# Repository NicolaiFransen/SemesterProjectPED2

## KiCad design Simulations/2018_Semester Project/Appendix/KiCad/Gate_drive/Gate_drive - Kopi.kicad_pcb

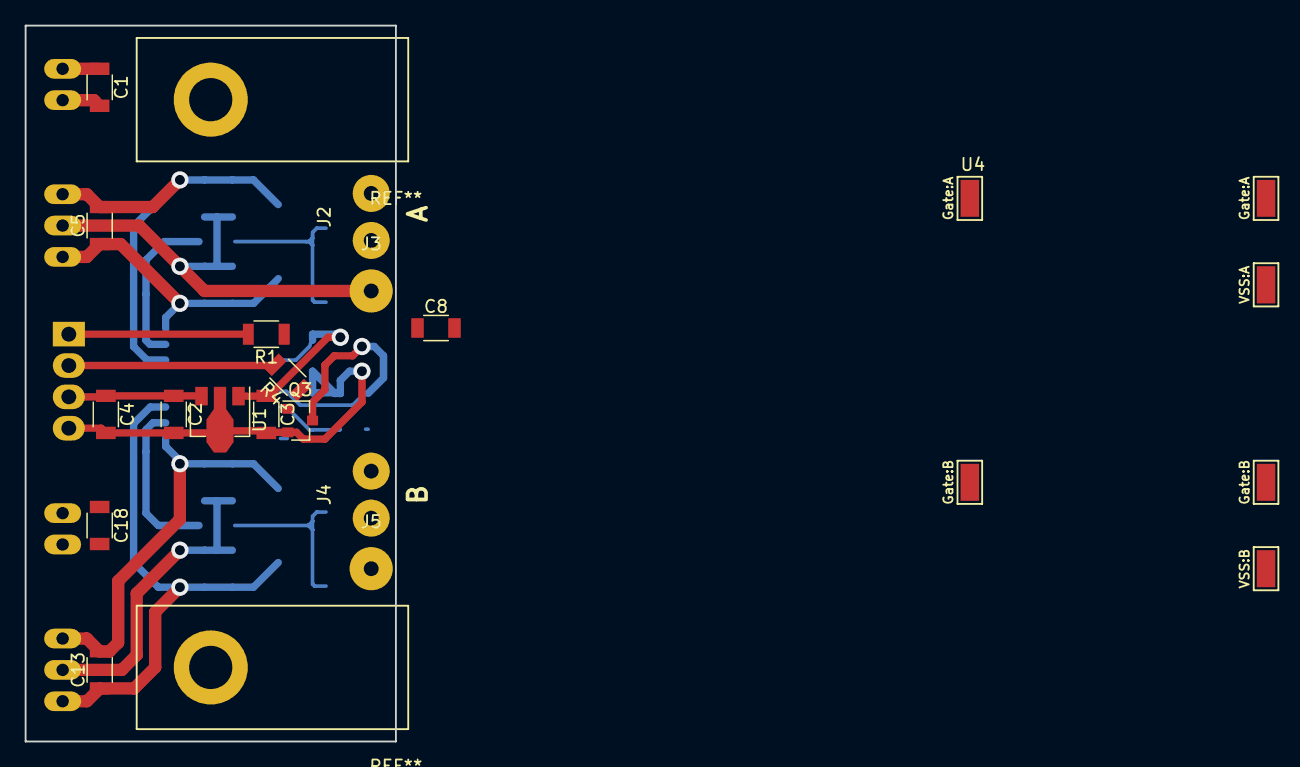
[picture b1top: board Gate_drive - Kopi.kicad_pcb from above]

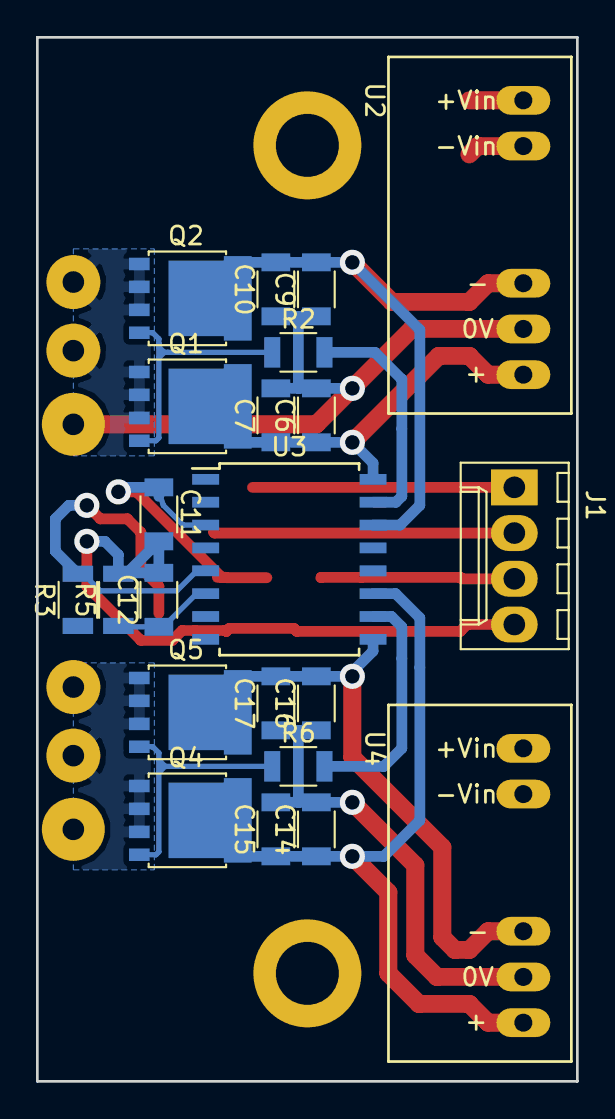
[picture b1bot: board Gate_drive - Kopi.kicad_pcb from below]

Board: 2 copper layers, 30.0 x 58.0 mm, 39 parts (22 on the bottom side), 21 nets.

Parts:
C1, C3, C7, C10, C11, C15, C17, C18: 100n; C_1206
C2: 330n; C_1206
C4, C5, C13: 10u; C_1206
C6, C9, C14, C16: 4.7u; C_1206
C8: 33p; C_1206
C12: 2.2n; C_1206
J1: Inputs; Molex_KK-6410-04_04x2.54mm_Straight
J2: Gate:A; SolderWirePad_2x_1-2mmDrill
J3: VSS:A; SolderWirePad_single_1-2mmDrill
J4: Gate:B; SolderWirePad_2x_1-2mmDrill
J5: VSS:B; SolderWirePad_single_1-2mmDrill
Q1, Q4: PHPT60415NY; SOT-669_LFPAK
Q2, Q5: PHPT60415PY; SOT-669_LFPAK
Q3: BC846A; SOT-23
R1: 47; R_1206
R2, R6: 1; R_1206
R3, R5: 100k; R_1206
R4: 5k6; R_1206
U1: L78L15ABUTR; SOT-89-3
U2, U4: MGJ2D241509SC; SIL_MGJ2
U3: UCC20520; SOIC-16W_7.5x10.3mm_Pitch1.27mm
U4#2: Gate_drive_board; Gate_driver_example

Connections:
+15V: C3.1, C11.1, R3.1, U1.1, U3.3, U3.8
+24V: C1.1, C2.1, C4.1, C18.1, J1.3, U1.3, U2.1, U4.1
/+15V:A: C5.1, C6.1, C7.1, Q1.5, U2.7, U3.16
/+15V:B: C13.1, C14.1, C15.1, Q4.5, U3.11, U4.7
/-8.7V:A: C5.2, C9.2, C10.2, Q2.5, U2.5, U3.14
/-8.7V:B: C13.2, C16.2, C17.2, Q5.5, U3.9, U4.5
/DT: C12.1, R5.1, U3.6
/ENABLE: J1.2, R4.2
/Gate:A: J2.1, Q1.1, Q1.2, Q1.3, Q2.1, Q2.2, Q2.3
/Gate:B: J4.1, Q4.1, Q4.2, Q4.3, Q5.1, Q5.2, Q5.3
/PWM: J1.1, R1.2
/VSS:A: C6.2, C7.2, C9.1, C10.1, J3.1, U2.6
/VSS:B: C14.2, C15.2, C16.1, C17.1, J5.1, U4.6
GND: C1.2, C2.2, C3.2, C4.2, C8.2, C11.2, C12.2, C18.2, J1.4, Q3.2, R5.2, U1.2, U2.2, U3.4, U4.2
unnamed: C8.1, R1.1, U3.1
unnamed: Q1.4, Q2.4, R2.1
unnamed: Q3.1, R4.1
unnamed: Q3.3, R3.2, U3.5
unnamed: Q4.4, Q5.4, R6.1
unnamed: R2.2, U3.15
unnamed: R6.2, U3.10

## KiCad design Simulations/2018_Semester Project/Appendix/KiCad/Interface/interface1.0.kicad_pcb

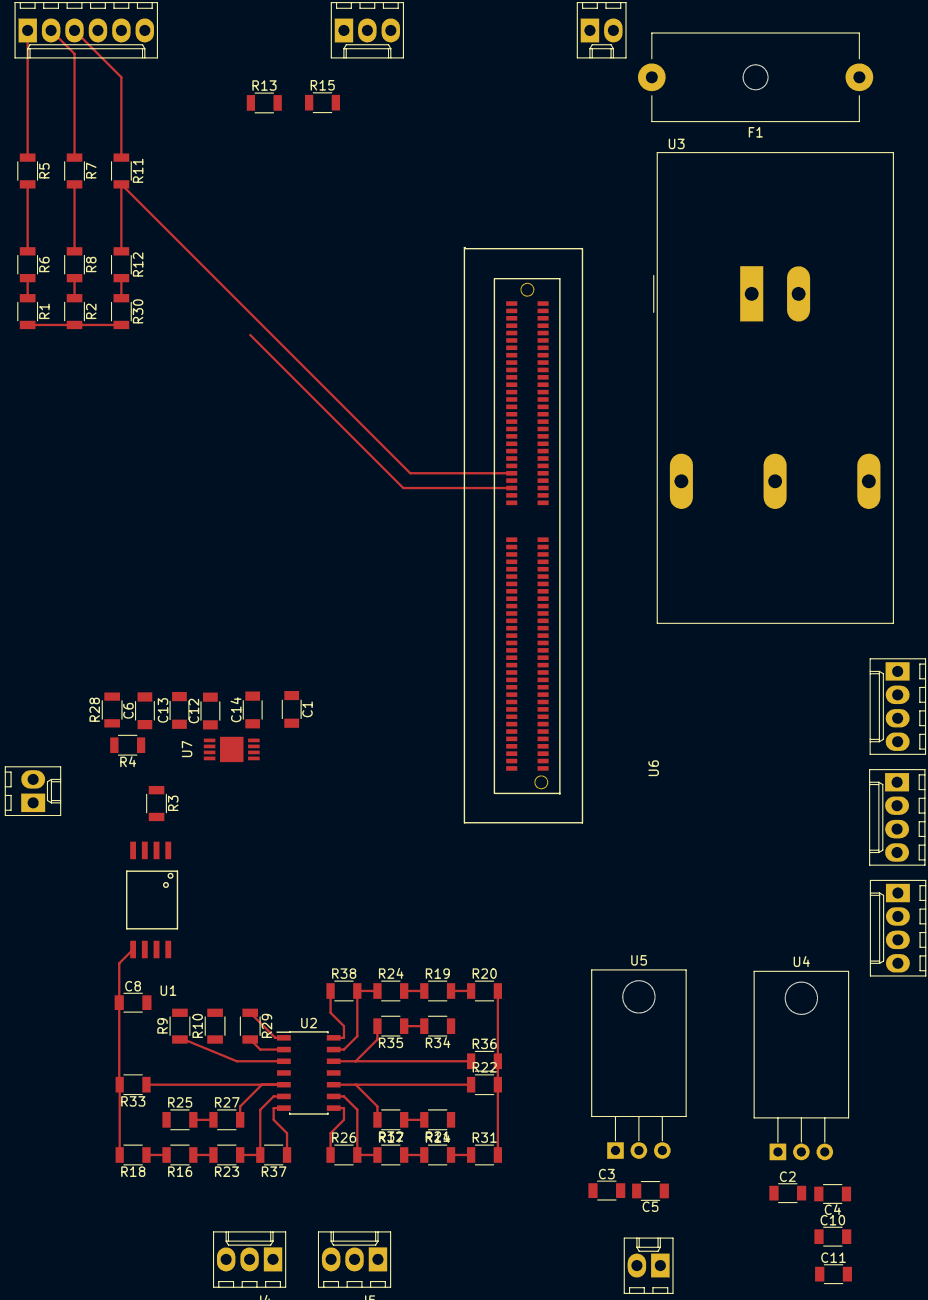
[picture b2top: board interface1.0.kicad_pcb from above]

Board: 2 copper layers, 68 parts (0 on the bottom side), 52 nets.

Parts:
C1, C8, C11: 0.1u; C_1206
C2, C3: 0.33uF; C_1206
C4, C5: 0.1uF; C_1206
C6: 750p; C_1206
C10, C12: 1u; C_1206
C13: 0.1; C_1206
C14: 10u; C_1206
F1: Fuse; Fuseholder5x20_horiz_open_Schurter_0031_8201
J1: Torque pedal; Molex_KK-6410-03_03x2.54mm_Straight
J2: 36V Supply; Molex_KK-6410-02_02x2.54mm_Straight
J3: Encoder; Molex_KK-6410-06_06x2.54mm_Straight
J4: Cur_Meas_Sig; Molex_KK-6410-03_03x2.54mm_Straight
J5: Cur_Meas_Supply; Molex_KK-6410-03_03x2.54mm_Straight
J6: Fan; Molex_KK-6410-02_02x2.54mm_Straight
J7: 24V Supply; Molex_KK-6410-02_02x2.54mm_Straight
J8: PWM3; Molex_KK-6410-04_04x2.54mm_Straight
J9: PWM2; Molex_KK-6410-04_04x2.54mm_Straight
J10: PWM1; Molex_KK-6410-04_04x2.54mm_Straight
R1, R2, R5, R6, R7, R8, R11, R12, R30: 1k; R_1206
R3, R22, R33, R36: 11k; R_1206
R4, R21, R25, R34: 62k; R_1206
R9, R10, R17, R23, R24, R26, R29, R37, R38: 10k; R_1206
R13: 560; R_1206
R14, R16, R19: 3; R_1206
R15: 56; R_1206
R18, R20, R31: 2; R_1206
R27, R32, R35: 330; R_1206
R28: 4.7k; R_1206
U1: ACPL-C870-000E
U2: LM324; SOIC-14_3.9x8.7mm_Pitch1.27mm
U3: TRACO+/-15; DCDC-Conv_TRACO_TEN10-XXXX_Dual
U4: L7805; TO-220-3_Horizontal
U5: TS7812; TO-220-3_Horizontal
U6: MicroCon_socket; HSEC8-160-01-L-DV-A
U7: MIC5282-5.0YMME; 8-Pin(ePad)MSOP

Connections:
+5VD: C1.2, C14.1, U1.1, U7.6, U7.8
+12V: C5.1, J6.1, U5.3
+15V: J5.1, U2.4, U3.3
+24V: C2.1, C3.1, F1.1, J8.3, J9.3, J10.3, U3.2, U4.1, U5.1
+36V: C12.1, J2.1, R3.1, U7.1
-15V: J5.3, U2.11, U3.5
A_Pnk: J3.1, R5.1
B_Grn: J3.2, R7.1
CurA_meas: J4.1, R16.1, R23.2
CurA_sig: R37.1, U2.7, U6.9
CurB_meas: J4.2, R14.1, R17.2
CurB_sig: R26.1, U2.8, U6.12
CurC_meas: J4.3, R19.1, R24.2
CurC_sig: R38.1, U2.14, U6.24
ENB_sig: J8.2, J9.2, J10.2, U6.60
EncA_sig: R5.2, R6.1, U6.68
EncB_sig: R7.2, R8.1, U6.70
EncZ_sig: R11.2, R12.1, U6.74
GND: C1.1, C6.2, C12.2, C13.2, C14.2, J2.2, R28.2, U1.3, U1.4, U3.1, U7.5
Gnd_Bl: C2.2, C3.2, C4.2, C5.2, C8.1, C10.1, C11.1, J1.2, J3.5, J3.6, J5.2, J6.2, J7.2, J8.4, J9.4, J10.4, R1.2, R2.2, R18.2, R20.2, R22.2, R30.2, R31.2, R33.2, R36.2, U1.5, U3.4, U4.2, U5.2, U6.19, U6.22, U6.38, U6.46
unnamed: C6.1, R3.2, R4.1, U1.2
unnamed: C13.1, U7.4
unnamed: F1.2, J7.1
unnamed: R1.1, R6.2
unnamed: R2.1, R8.2
unnamed: R9.1, U2.3
unnamed: R9.2, U1.7
unnamed: R10.1, R29.2, U2.2
unnamed: R10.2, U1.6
unnamed: R12.2, R30.1
unnamed: R13.2, R15.1
unnamed: R14.2, R31.1
unnamed: R16.2, R18.1
unnamed: R17.1, R26.2, U2.9
unnamed: R19.2, R20.1
unnamed: R21.2, R32.1
unnamed: R22.1, R32.2, U2.10
unnamed: R23.1, R37.2, U2.6
unnamed: R24.1, R38.2, U2.13
unnamed: R25.2, R27.1
unnamed: R27.2, R33.1, U2.5
unnamed: R4.2, R28.1
unnamed: R34.2, R35.1
unnamed: R35.2, R36.1, U2.12
PWM1_sig: J10.1, U6.49
PWM2_sig: J9.1, U6.50
PWM3_sig: J8.1, U6.53
Ped_R: J1.1, R15.2
Ped_sig_Bl: J1.3, U6.14
Vcc_R: C4.1, C8.2, C10.2, C11.2, J3.4, R13.1, R21.1, R25.1, R34.1, U1.8, U4.3, U6.48
Vol_sig: R29.1, U2.1, U6.26
Z_Wht: J3.3, R11.1
